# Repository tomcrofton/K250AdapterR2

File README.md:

# K250AdapterR2
Single Board version of K250 Adapter

Concerning R3/R4, you only need to populate one of them.

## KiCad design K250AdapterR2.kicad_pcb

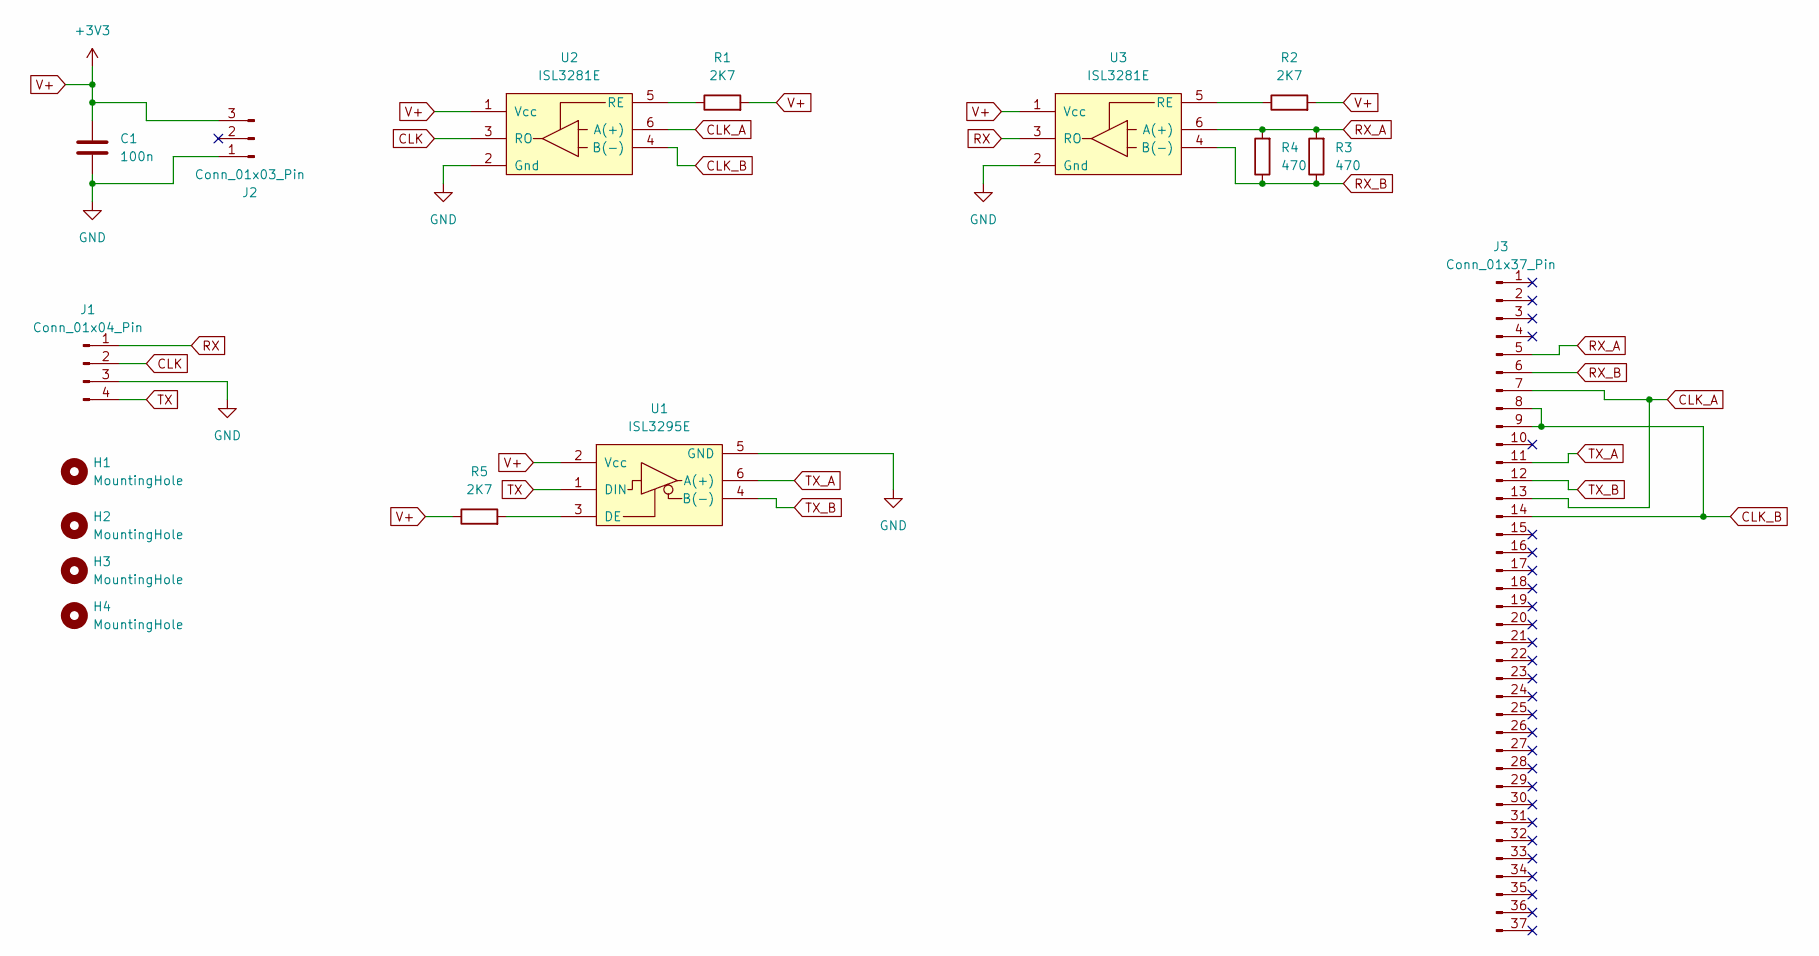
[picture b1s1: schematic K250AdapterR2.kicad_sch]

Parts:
C1: 100n; C_1206_3216Metric
H1, H2, H3, H4: MountingHole; MountingHole_2.2mm_M2
J1: Conn_01x04_Pin; PinHeader_1x04_P2.54mm_Vertical
J2: Conn_01x03_Pin; PinHeader_1x03_P2.54mm_Vertical
J3: Conn_01x37_Pin; DSUB-37_Male_Horizontal_P2.77x2.84mm_EdgePinOffset7.70mm_Ho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
R1, R2, R5: 2K7; R_0805_2012Metric
R3, R4: 470; R_1206_3216Metric
U1: ISL3295E; SOT-23-6
U2, U3: ISL3281E; SOT-23-6

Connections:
CLK: J1.2, U2.3 (RO)
CLK_A: J3.7, J3.13, U2.6 (A(+))
CLK_B: J3.8, J3.9, J3.14, U2.4 (B(-))
GND: C1.2, J1.3, J2.1, U1.5 (GND), U2.2 (Gnd), U3.2 (Gnd)
unnamed: R5.2, U1.3 (DE)
unnamed: R1.1, U2.5 (RE)
unnamed: R2.1, U3.5 (RE)
RX: J1.1, U3.3 (RO)
RX_A: J3.5, R3.2, R4.2, U3.6 (A(+))
RX_B: J3.6, R3.1, R4.1, U3.4 (B(-))
TX: J1.4, U1.1 (DIN)
TX_A: J3.11, U1.6 (A(+))
TX_B: J3.12, U1.4 (B(-))
V+: C1.1, J2.3, R1.2, R2.2, R5.1, U1.2 (Vcc), U2.1 (Vcc), U3.1 (Vcc)

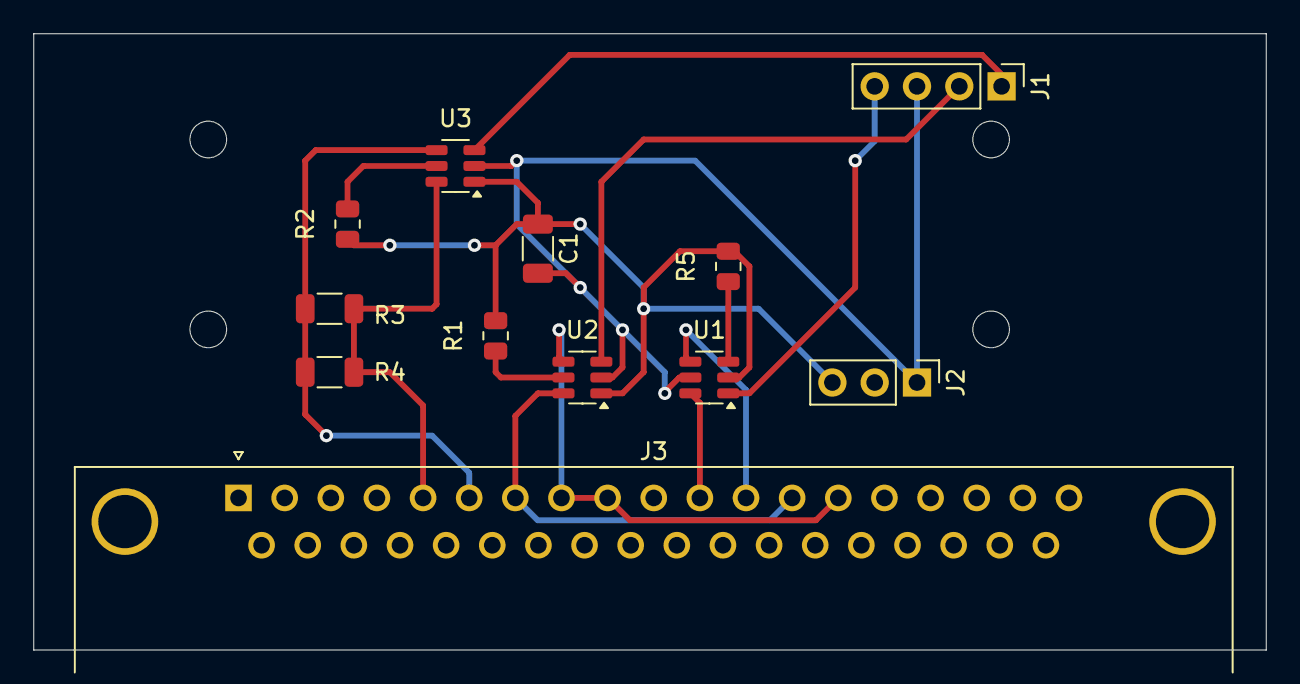
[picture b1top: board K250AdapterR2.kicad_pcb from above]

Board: 2 copper layers, 74.0 x 37.0 mm, 16 parts (0 on the bottom side), 14 nets.
